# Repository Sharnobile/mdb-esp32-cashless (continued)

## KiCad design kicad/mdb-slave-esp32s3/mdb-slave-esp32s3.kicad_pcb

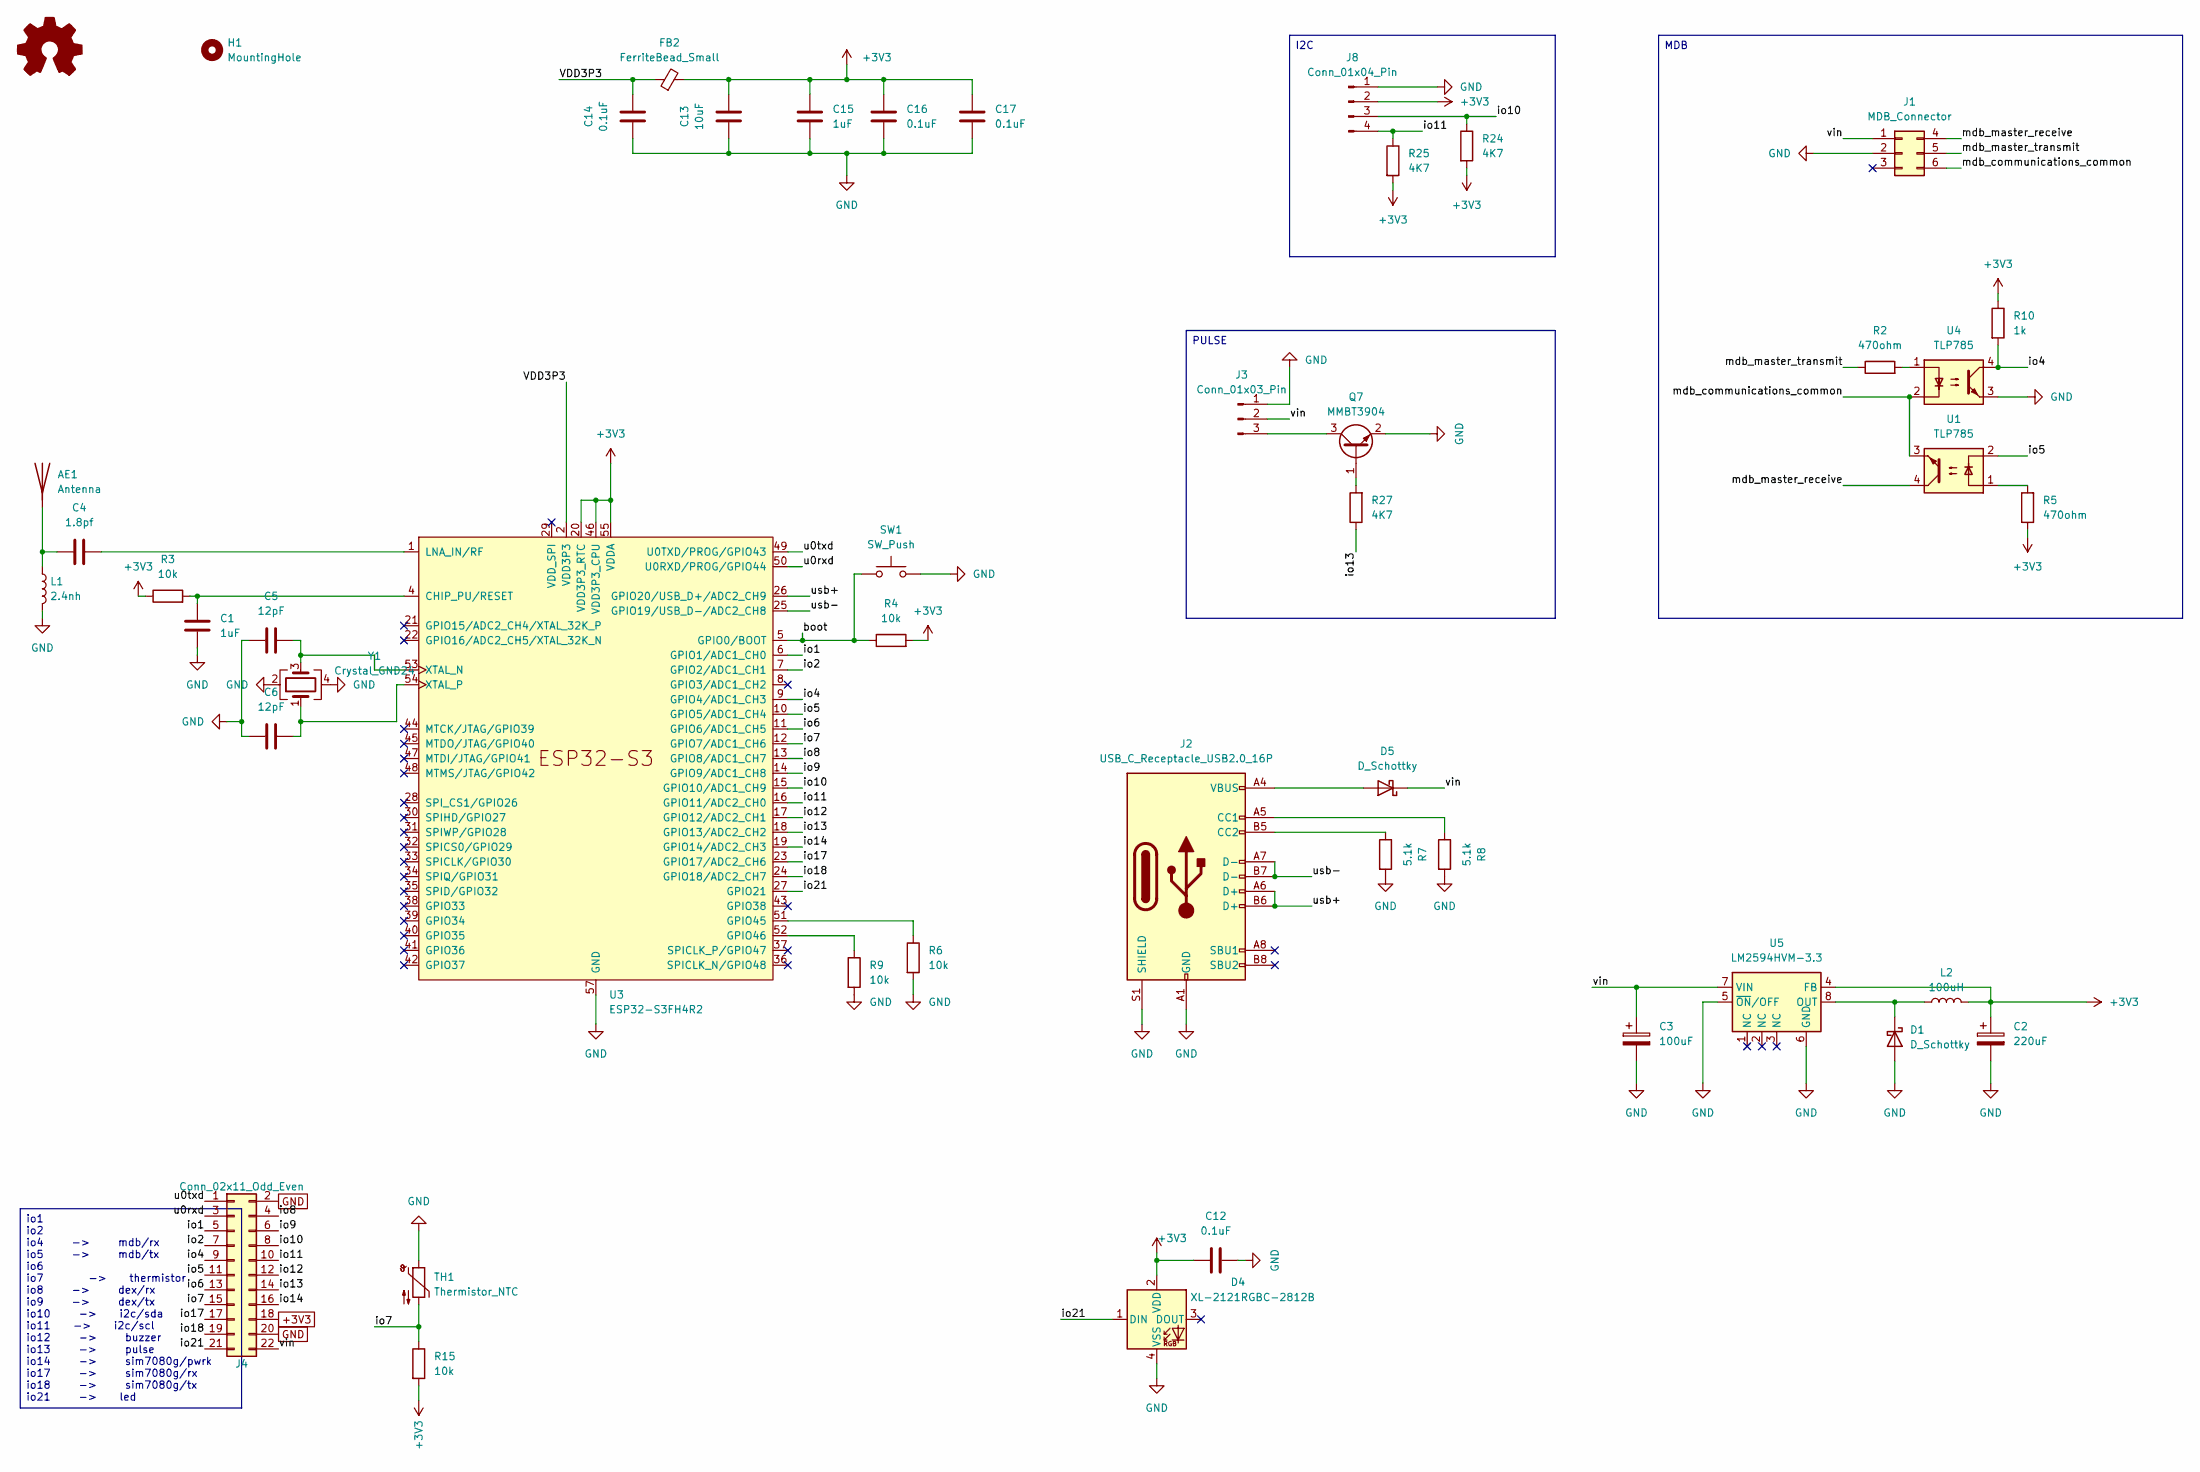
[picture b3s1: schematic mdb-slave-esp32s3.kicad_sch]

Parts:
AE1: Antenna; Texas_SWRA117D_2.4GHz_Left
C1, C15: 1uF; C_0603_1608Metric; LCSC# C6119849
C2: 220uF; CP_EIA-3528-21_Kemet-B; LCSC# C30242
C3: 100uF; CP_Elec_6.3x5.8; LCSC# C128464
C4: 1.8pf; C_0603_1608Metric; LCSC# C376773
C5, C6: 12pF; C_0603_1608Metric; LCSC# C363546
C12, C14, C16, C17: 0.1uF; C_0603_1608Metric; LCSC# C5137636
C13: 10uF; C_0603_1608Metric; LCSC# C6119864
D1, D5: D_Schottky; D_SOD-123; LCSC# C18195164
D4: XL-2121RGBC-2812B; LED_WS2812B-2020_PLCC4_2.0x2.0mm; LCSC# C5349957
FB2: FerriteBead_Small; L_0603_1608Metric; LCSC# C304319
H1: MountingHole; MountingHole_2.1mm
J1: MDB_Connector; Molex_Mini-Fit_Jr_5566-06A_2x03_P4.20mm_Vertical; LCSC# C22365701
J2: USB_C_Receptacle_USB2.0_16P; USB_C_Receptacle_G-Switch_GT-USB-7010ASV; LCSC# C2988369
J3: Conn_01x03_Pin; JST_PH_B3B-PH-K_1x03_P2.00mm_Vertical; LCSC# C131339
J4: Conn_02x11_Odd_Even; PinHeader_2x11_P2.54mm_Vertical
J8: Conn_01x04_Pin; JST_PH_B4B-PH-K_1x04_P2.00mm_Vertical; LCSC# C131334
L1: 2.4nh; L_0603_1608Metric; LCSC# C2042508
L2: 100uH; L_7.3x7.3_H3.5; LCSC# C182195
Q7: MMBT3904; SOT-23; LCSC# C916374
R2, R5: 470ohm; R_0603_1608Metric; LCSC# C114669
R3, R4, R6, R9, R15: 10k; R_0603_1608Metric; LCSC# C98220
R7, R8: 5.1k; R_0603_1608Metric; LCSC# C394543
R10: 1k; R_0603_1608Metric; LCSC# C2907113
R24, R25, R27: 4K7; R_0603_1608Metric; LCSC# C23162
SW1: SW_Push; SW_Tactile_SPST_NO_Straight_CK_PTS636Sx25SMTRLFS; LCSC# C42435421
TH1: Thermistor_NTC; R_0603_1608Metric; LCSC# C13564
U1, U4: TLP785; SOP-4_3.8x4.1mm_P2.54mm; LCSC# C128776
U3: ESP32-S3FH4R2; QFN-56-1EP_7x7mm_P0.4mm_EP4x4mm; LCSC# C3013940
U5: LM2594HVM-3.3; SOIC-8_3.9x4.9mm_P1.27mm; LCSC# C18057294
Y1: Crystal_GND24; Crystal_SMD_3225-4Pin_3.2x2.5mm; LCSC# C7294599

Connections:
+3V3: C2.1, C12.2, C13.2, C15.2, C16.1, C17.1, D4.2 (VDD), FB2.2, J4.18, J8.2, L2.2, R3.1, R4.2, R5.1, R10.1, R15.2, R24.2, R25.2, U3.20 (VDD3P3_RTC), U3.46 (VDD3P3_CPU), U3.55 (VDDA), U3.56 (VDDA), U5.4 (FB)
/boot: R4.1, SW1.1, U3.5 (GPIO0/BOOT)
/io1: J4.5, U3.6 (GPIO1/ADC1_CH0)
/io2: J4.7, U3.7 (GPIO2/ADC1_CH1)
/io4: J4.9, R10.2, U3.9 (GPIO4/ADC1_CH3), U4.4
/io5: J4.11, U1.2, U3.10 (GPIO5/ADC1_CH4)
/io6: J4.13, U3.11 (GPIO6/ADC1_CH5)
/io7: J4.15, R15.1, TH1.2, U3.12 (GPIO7/ADC1_CH6)
/io8: J4.4, U3.13 (GPIO8/ADC1_CH7)
/io9: J4.6, U3.14 (GPIO9/ADC1_CH8)
/io10: J4.8, J8.3, R24.1, U3.15 (GPIO10/ADC1_CH9)
/io11: J4.10, J8.4, R25.1, U3.16 (GPIO11/ADC2_CH0)
/io12: J4.12, U3.17 (GPIO12/ADC2_CH1)
/io13: J4.14, R27.1, U3.18 (GPIO13/ADC2_CH2)
/io14: J4.16, U3.19 (GPIO14/ADC2_CH3)
/io17: J4.17, U3.23 (GPIO17/ADC2_CH6)
/io18: J4.19, U3.24 (GPIO18/ADC2_CH7)
/io21: D4.1 (DIN), J4.21, U3.27 (GPIO21)
/mdb_communications_common: J1.6, U1.3, U4.2
/mdb_master_receive: J1.4, U1.4
/mdb_master_transmit: J1.5, R2.1
/u0rxd: J4.3, U3.50 (U0RXD/PROG/GPIO44)
/u0txd: J4.1, U3.49 (U0TXD/PROG/GPIO43)
/usb+: J2.A6 (D+), J2.B6 (D+), U3.26 (GPIO20/USB_D+/ADC2_CH9)
/usb-: J2.A7 (D-), J2.B7 (D-), U3.25 (GPIO19/USB_D-/ADC2_CH8)
/vin: C3.1, D5.1 (K), J1.1, J3.2, J4.22, U5.7 (VIN)
GND: C1.2, C2.2, C3.2, C5.1, C6.1, C12.1, C13.1, C14.1, C15.1, C16.2, C17.2, D1.2 (A), D4.4 (VSS), J1.2, J2.A1 (GND), J2.A12 (GND), J2.B1 (GND), J2.B12 (GND), J2.S1 (SHIELD), J3.1, J4.2, J4.20, J8.1, L1.2, Q7.2 (E), R6.2, R7.2, R8.2, R9.2, SW1.2, TH1.1, U3.57 (GND), U4.3, U5.5 (~ON/OFF), U5.6 (GND), Y1.2, Y1.4
unnamed: AE1.1 (A), C4.1, L1.1
unnamed: D1.1 (K), L2.1, U5.8 (OUT)
unnamed: D5.2 (A), J2.A4 (VBUS), J2.A9 (VBUS), J2.B4 (VBUS), J2.B9 (VBUS)
unnamed: J2.A5 (CC1), R8.1
unnamed: J2.B5 (CC2), R7.1
unnamed: J3.3, Q7.3 (C)
unnamed: Q7.1 (B), R27.2
unnamed: R2.2, U4.1
unnamed: R5.2, U1.1
unnamed: C1.1, R3.2, U3.4 (CHIP_PU/RESET)
unnamed: R6.1, U3.51 (GPIO45)
unnamed: R9.1, U3.52 (GPIO46)
unnamed: C4.2, U3.1 (LNA_IN/RF)
unnamed: C5.2, U3.53 (XTAL_N), Y1.3
unnamed: C6.2, U3.54 (XTAL_P), Y1.1
VDD3P3: C14.2, FB2.1, U3.2 (VDD3P3), U3.3 (VDD3P3)

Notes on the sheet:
io1 io2 io4 -> mdb/rx io5 -> mdb/tx io6 io7 -> thermistor io8 -> dex/rx io9 -> dex/tx io10 -> i2c/sda io11 -> i2c/scl io12 -> buzzer io13 -> pulse io14 -> sim7080g/pwrk io17 -> sim7080g/rx io18 -> sim7080g/tx io21 -> led
PULSE
I2C
MDB

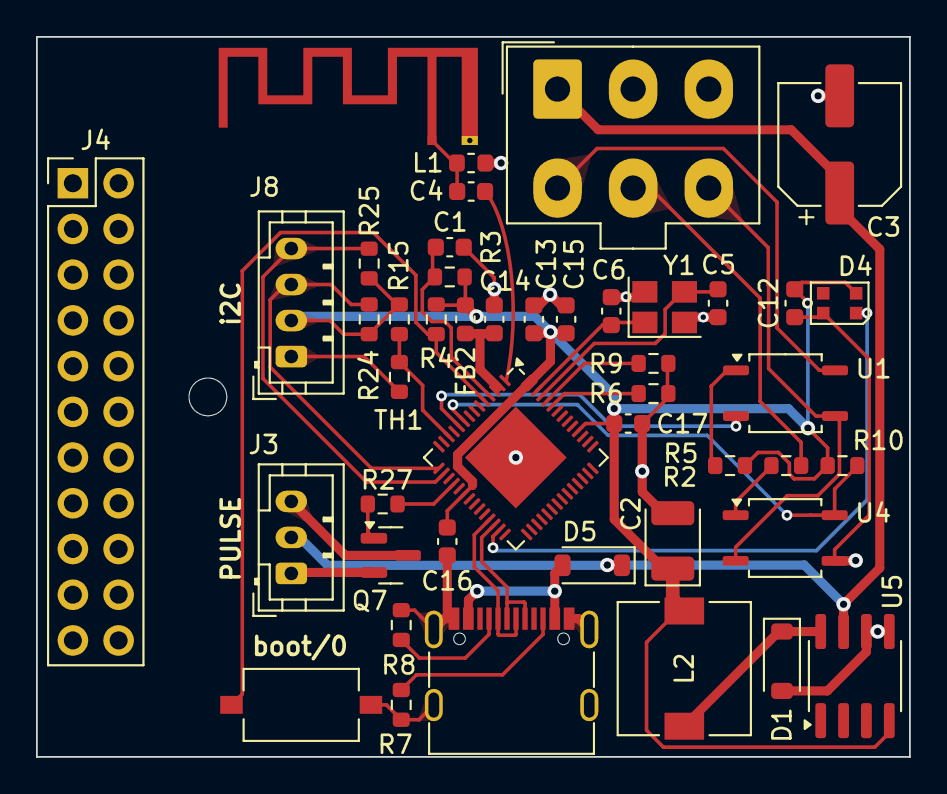
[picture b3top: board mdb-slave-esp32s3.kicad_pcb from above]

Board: 2 copper layers, 48.5 x 40.0 mm, 46 parts (0 on the bottom side), 43 nets.

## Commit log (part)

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2026-06-01 test: pin vitest timezone to UTC for deterministic date logic
2026-06-01 feat(nayax): pure LCS aligner for sequence reconciliation
2026-06-01 feat(nayax): per-machine aligner with day-bucket size guard
2026-06-01 feat(nayax): bufferRange helper for the DB query window
2026-06-01 feat(nayax): pure day-grouping helper for the differences list
2026-06-02 i18n(nayax): stock-neutral import body + adjust-stock checkbox strings
2026-06-02 feat(nayax): bulkImportMissing threads adjustStock to insert_manual_sale
2026-06-02 feat(nayax): import-confirm checkbox to also reduce tray stock (default off)
2026-06-02 feat(db): suppressed_sales audit table for brownout dedup
2026-06-02 feat(webhook): pure decideSuppress for brownout duplicate detection
2026-06-02 feat(webhook): drop brownout duplicate re-reports into suppressed_sales
2026-06-02 feat(pwa): useSuppressedSales composable
2026-06-02 i18n(pwa): auto-removed duplicates strings
2026-06-02 feat(pwa): device-health auto-removed-duplicates card
2026-06-04 fix(ios): show slot capacity in per-machine pack tab meta line
    The per-machine packing list only showed "needs 2" while the combined
    "all" view showed "needs 2 / 5". Add the slot capacity to the
    per-machine meta line so the maximum quantity is visible in both views.
2026-06-04 fix(ios): add SuppressedSale.swift to Xcode target
    The SuppressedSale model file existed on disk but was never added to
    the VMflow target in project.pbxproj, so the compiler couldn't find the
    type. This caused "Cannot find type 'SuppressedSale'" errors in
    MachineDetailViewModel, MachineDetailView and RealtimeService, plus a
    cascade 'subscript(dynamicMember:)' error in the view body.
    Wire the file into the build (PBXBuildFile, PBXFileReference, Models
2026-06-06 feat(db): snapshot product_id on suppressed_sales (+ backfill)
2026-06-06 feat(webhook): snapshot matched sale's product_id onto suppressed_sales
2026-06-09 mqtt-webhook: gate brownout-duplicate suppression on a corroborating reboot
    A time_uncertain sale was auto-removed whenever any same-key sale
    (item_number/item_price/channel) existed within ±30s. That heuristic
    cannot distinguish a real brownout re-report from a legitimate repeat
    purchase, so genuine sales (e.g. a 3rd Jack Daniel's & Cola 26s after the
    2nd) were wrongly suppressed.
    A brownout re-report only ever follows an actual device reset, so it has
2026-06-11 feat(ios): dashboard recent-activity feed (sales+refills+intakes+tours) with infinite scroll
2026-06-11 updated deals files
2026-06-14 feat(db): deal plausibility filter (get_suppressed_offer_keys) + exclude from get_new_deal_keys
2026-06-14 feat(deal-search): exclude implausible (above-max-EK) offers from new-deal push count
    Re-counts newly-first-seen offers through get_suppressed_offer_keys before
    the new-deals push fires, so offers whose deal price exceeds the highest
    recorded EK gross for ALL matched products never inflate the push count.
    No EK data -> empty suppressed set -> no-op (backward compatible).
    Manual check: with a product whose recorded EK gross is below a freshly-
    inserted offer's deal_price, a scheduled deal-search run must not include
2026-06-14 feat(pwa): SupplierCombobox (name autocomplete + inline create)
2026-06-14 feat(pwa): PurchasePricesSection (history, add/edit, net/gross, margin)
2026-06-14 feat(pwa): show PurchasePricesSection in product edit modal
2026-06-14 feat(pwa): EK/margin column in product list
2026-06-14 i18n(pwa): purchase-price + supplier strings (de/en)
